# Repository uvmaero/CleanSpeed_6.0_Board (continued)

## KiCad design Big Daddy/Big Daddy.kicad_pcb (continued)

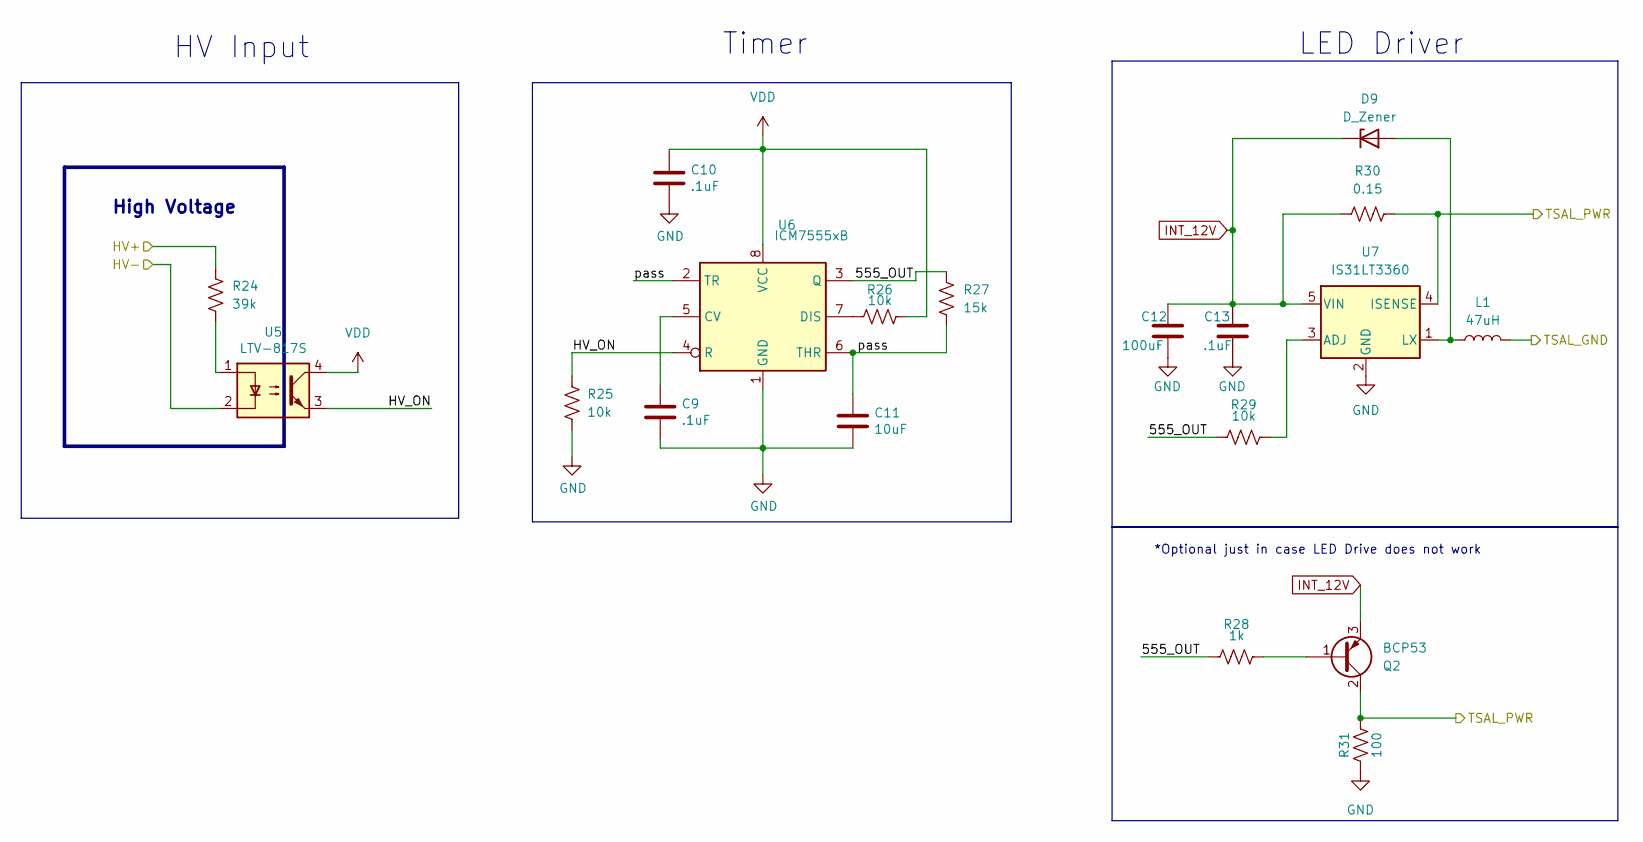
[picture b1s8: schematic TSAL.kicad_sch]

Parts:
C9, C10, C13: .1uF; C_0603_1608Metric_Pad1.08x0.95mm_HandSolder; Manufacturer_Part_Number CC0603KRX7R7BB104; Digikey part number 311-1088-1-ND
C11: 10uF; C_0603_1608Metric_Pad1.08x0.95mm_HandSolder; Manufacturer_Part_Number CL10A106KQ8NNNC; Digikey part number 1276-1038-1-ND
C12: 100uF; C_0603_1608Metric_Pad1.08x0.95mm_HandSolder
D9: D_Zener; D_SOD-123; Manufacturer_Part_Number MMSZ5231B-7-F; Digikey part number MMSZ5231B-FDICT-ND
L1: 47uH; L_0603_1608Metric_Pad1.05x0.95mm_HandSolder; Manufacturer_Part_Number LBMF1608T470K; Digikey part number 587-1716-1-ND
Q2: BCP53; SOT-223-3_TabPin2; Manufacturer_Part_Number BCP53; Digikey part number BCP53FSCT-ND
R24: 39k; R_Axial_DIN0414_L11.9mm_D4.5mm_P15.24mm_Horizontal; Manufacturer_Part_Number CF12JT39K0; Digikey part number CF12JT39K0CT-ND
R25, R26, R29: 10k; R_0603_1608Metric_Pad0.98x0.95mm_HandSolder; Manufacturer_Part_Number RK73H1JTTD1002F; Digikey part number 2019-RK73H1JTTD1002FCT-ND
R27: 15k; R_0603_1608Metric_Pad0.98x0.95mm_HandSolder; Manufacturer_Part_Number ERA-3AEB153V; Digikey part number P15KDBCT-ND
R28: 1k; R_0603_1608Metric_Pad0.98x0.95mm_HandSolder; Manufacturer_Part_Number RMCF0603FT1K00; Digikey part number RMCF0603FT1K00CT-ND
R30: 0.15; R_0603_1608Metric_Pad0.98x0.95mm_HandSolder; Manufacturer_Part_Number RL0603FR-070R15L; Digikey part number 311-.15QCT-ND
R31: 100; R_1206_3216Metric_Pad1.30x1.75mm_HandSolder; Manufacturer_Part_Number ERJ-8ENF1000V; Digikey part number P100FCT-ND
U5: LTV-817S; SMDIP-4_W9.53mm; Manufacturer_Part_Number LTV-817S; Digikey part number 160-1367-5-ND
U6: ICM7555xB; SOIC-8_3.9x4.9mm_P1.27mm; Manufacturer_Part_Number ICM7555CBAZ-T; Digikey part number ICM7555CBAZ-TCT-ND
U7: IS31LT3360; SOT-89-5; Manufacturer_Part_Number IS31LT3360-SDLS4-TR; Digikey part number 2521-IS31LT3360-SDLS4-TRCT-ND

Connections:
/Connectors/TSAL_GND: L1.2; also elsewhere on the board
/Connectors/TSAL_PWR: Q2.2 (C), Q2.4 (C), R30.2, R31.2, U7.4 (ISENSE); also elsewhere on the board
/High Voltage/TSAL/555_OUT: R27.1, R28.1, R29.1, U6.3 (Q)
/High Voltage/TSAL/HV+: R24.1; also elsewhere on the board
/High Voltage/TSAL/HV-: U5.2; also elsewhere on the board
/High Voltage/TSAL/HV_ON: R25.1, U5.3, U6.4 (R)
/High Voltage/TSAL/pass: C11.1, R27.2, U6.2 (TR), U6.6 (THR)
GND: C9.2, C10.2, C11.2, C12.1, C13.1, R25.2, R31.1, U6.1 (GND), U7.2 (GND); also elsewhere on the board
INT_12V: C12.2, C13.2, D9.1 (K), Q2.3 (E), R30.1, U7.5 (VIN); also elsewhere on the board
unnamed: D9.2 (A), L1.1, U7.1 (LX)
unnamed: Q2.1 (B), R28.2
unnamed: R24.2, U5.1
unnamed: C9.1, U6.5 (CV)
unnamed: R26.1, U6.7 (DIS)
unnamed: R29.2, U7.3 (ADJ)
VDD: C10.1, R26.2, U5.4, U6.8 (VCC); also elsewhere on the board

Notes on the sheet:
*Optional just in case LED Drive does not work
LED Driver
High Voltage
HV Input
Timer

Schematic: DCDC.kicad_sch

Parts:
C14, C15: 0.68uF; C_Rect_L18.0mm_W8.0mm_P15.00mm_FKS3_FKP3
C16, C17: 4700uF; C_Radial_D18.0mm_H35.5mm_P7.50mm
L2: 1uH; L_1008_2520Metric_Pad1.43x2.20mm_HandSolder; Manufacturer_Part_Number LQM2HPN1R0MG0L; Digikey part number 490-5112-1-ND
L3: 0.15uH; L_0805_2012Metric_Pad1.15x1.40mm_HandSolder; Manufacturer_Part_Number CE201210-R15J; Digikey part number CE201210-R15JCT-ND
R35, R40: 1; R_2512_6332Metric_Pad1.40x3.35mm_HandSolder; Manufacturer_Part_Number RK73H1JTTD1002F; Digikey part number 2019-RK73H1JTTD1002FCT-ND
R36: 300; R_0603_1608Metric_Pad0.98x0.95mm_HandSolder; Manufacturer_Part_Number ERJ-3GEYJ301V; Digikey part number P300GCT-ND
R37, R38, R39: 1k; R_0603_1608Metric_Pad0.98x0.95mm_HandSolder; Manufacturer_Part_Number RMCF0603FT1K00; Digikey part number RMCF0603FT1K00CT-ND
RV1: 50k TC33x-2-503E; Potentiometer_Bourns_TC33X_Vertical; Manufacturer_Part_Number TC33X-2-503E; Digikey part number TC33X-503ECT-ND
U8: Vicor_AERO; vicor-socket-no-cutouts
U9: LTV-817S; SMDIP-4_W9.53mm; Manufacturer_Part_Number LTV-817S; Digikey part number 160-1367-5-ND
U10: TLP184; MFSOP6-4_4.4x3.6mm_P1.27mm; Manufacturer_Part_Number TLP184(BL-TPL,SE; Digikey part number TLP184(BL-TPLSECT-ND

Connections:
/Fusing/Vicor_In: C17.1, L3.2, R40.1; also elsewhere on the board
/High Voltage/DCDC/EN_HV: U8.3 (EN), U9.4
/High Voltage/DCDC/FAULT_HV: R37.2, U8.4 (FT)
/High Voltage/DCDC/HV+: L2.1, R35.2; also elsewhere on the board
/High Voltage/DCDC/HV-: C14.2, C15.2, RV1.1, U8.5 (-IN), U9.3, U10.3; also elsewhere on the board
/High Voltage/DCDC/TRIM_HV: R36.1, U8.2 (TR)
/High Voltage/Vicor_Enable: R38.1, R39.2; also elsewhere on the board
/High Voltage/Vicor_Fault: U10.6; also elsewhere on the board
GND: C16.2, C17.2, U8.8 (-OUT), U9.2, U10.4; also elsewhere on the board
unnamed: R36.2, RV1.2
unnamed: R37.1, U10.1
unnamed: R38.2, U9.1
unnamed: C14.1, C15.1, L2.2, R35.1, U8.1 (+IN)
unnamed: C16.1, L3.1, R40.2, U8.9 (+OUT)
VDD: R39.1; also elsewhere on the board

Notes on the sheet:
HV Side is pulled high enternally, optoisolator turns on (with high signal) to pull en_hv low
Willem Hillier UVM AERO 3/5/2019
Trim Control
Input Filtering
HV->12V DC-DC
DC/DC out
Output Filtering
HV Danger!
Pull high to disable
500V-rated caps
HV-Interface
FAULT_HV can only supply 4mA absolute max, hence the different optocoupler choice.

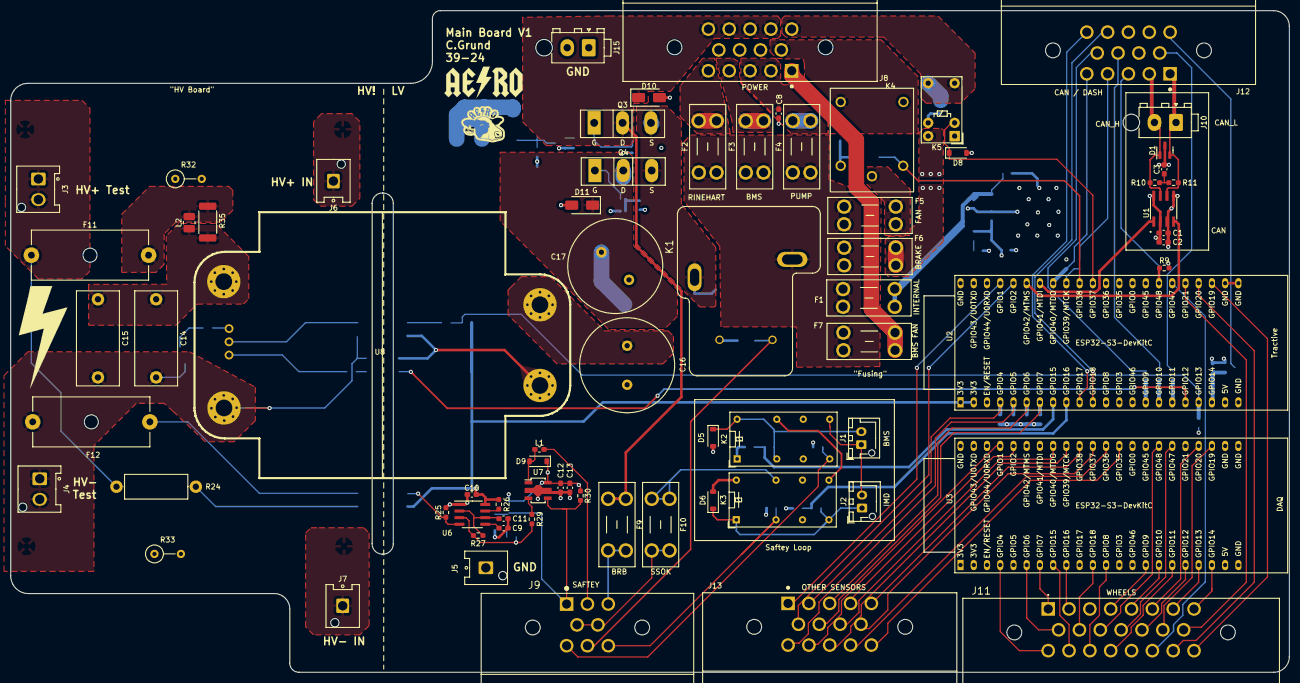
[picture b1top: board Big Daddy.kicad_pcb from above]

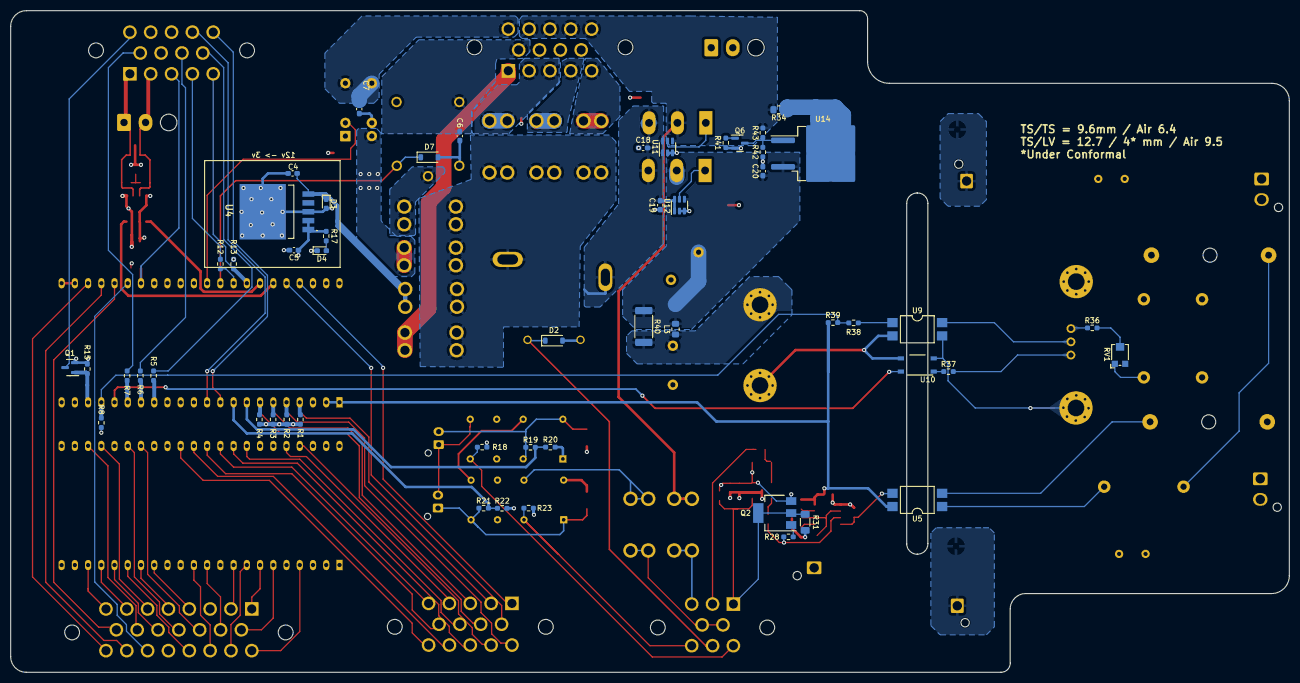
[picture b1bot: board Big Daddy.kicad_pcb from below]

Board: 4 copper layers, 245.4 x 126.9 mm, 124 parts (52 on the bottom side), 115 nets.

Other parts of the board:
Q6: MMBT2222; SOT-23
R41: 100; R_0603_1608Metric_Pad0.98x0.95mm_HandSolder

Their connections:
GND: Q6.2 (E), R41.2; also elsewhere on the board
unnamed: Q6.1 (B), R41.1

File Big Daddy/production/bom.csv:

Designator,Footprint,Quantity,Value,LCSC Part #
"C1, C10, C13, C18, C19, C2, C20, C3, C9",0603,9,.1uF,
"C11, C4, C6, C7, C8",0603,5,10uF,
C12,0603,1,100uF,
"C14, C15",C_Rect_L18.0mm_W8.0mm_P15.00mm_FKS3_FKP3,2,0.68uF,
"C16, C17",C_Radial_D18.0mm_H35.5mm_P7.50mm,2,4700uF,
C5,0603,1,22uF,
D1,SOT-23,1,DESD2CAN2SOQ-7,
"D10, D11",D_SMA,2,SS16,
"D2, D5, D6, D7, D8",D_SOD-123,5,1N4148W,
D3,0603,1,TS4148C RZG,
D4,0603,1,LED,
D9,D_SOD-123,1,D_Zener,
"F1, F4, F6, F7",Fuseholder_Blade_Mini_Keystone_3568,4,2A,
"F10, F9",Fuseholder_Blade_Mini_Keystone_3568,2,1A,
F11,Fuseholder_Cylinder-5x20mm_Schurter_0031_8201_Horizontal_Open_3d,1,5A,
F12,Fuseholder_Cylinder-5x20mm_Schurter_0031_8201_Horizontal_Open_3d,1,1A,
F2,Fuseholder_Blade_Mini_Keystone_3568,1,10A,
"F3, F5",Fuseholder_Blade_Mini_Keystone_3568,2,5A,
J1,JST_XH_B2B-XH-AM_1x02_P2.50mm_Vertical,1,BMS Button,
"J10, J15",TE_MATE-N-LOK_1-770866-x_1x02_P4.14mm_Vertical,2,Conn_01x02,
J11,TE_1-770669-1_23pin_Horizontal,1,Conn_01x23,
"J12, J13, J8",TE_1-776266-1_14pin_Horizontal,3,Conn_01x14,
J2,JST_XH_B2B-XH-AM_1x02_P2.50mm_Vertical,1,IMD Button,
J3,Hirose_DF63R-2P-3.96DSA_1x02_P3.96mm_Vertical,1,HV+,
J4,Hirose_DF63R-2P-3.96DSA_1x02_P3.96mm_Vertical,1,HV-,
J5,Hirose_DF63M-1P-3.96DSA_1x01_P3.96mm_Vertical,1,GND,
J6,Hirose_DF63M-1P-3.96DSA_1x01_P3.96mm_Vertical,1,HV+,
J7,Hirose_DF63M-1P-3.96DSA_1x01_P3.96mm_Vertical,1,HV-,
J9,TE_1-776280-1_8pin_Horizontal,1,Conn_01x08,
K1,RELAY_T9VV1K15-12S,1,T9VV1K15-12S,
"K2, K3",Relay_DPDT_Omron_G5V-2,2,G5V-2,
K4,J1071AS3VDC,1,J107,
K5,Relay_SPDT_Omron_G5V-1,1,G5V-1,
L1,0603,1,47uH,
L2,1008,1,1uH,
L3,0805,1,0.15uH,
Q1,SOT-23,1,2N7002,
Q2,SOT-223-3_TabPin2,1,BCP53,
"Q3, Q4",TO-247-3_Vertical_GDS,2,IXFH34N65X2,
Q6,SOT-23,1,MMBT2222,
"R1, R13, R15, R18, R2, R23, R25, R26, R29, R3, R4, R8, R9",0603,13,10k,
"R10, R11",0603,2,60,
"R12, R17, R5, R6, R7",0603,5,330,
"R19, R21",0603,2,5.97k,
"R20, R22",0603,2,2.2k,
R24,R_Axial_DIN0414_L11.9mm_D4.5mm_P15.24mm_Horizontal,1,39k,
R27,0603,1,15k,
"R28, R37, R38, R39",0603,4,1k,
R30,0603,1,0.15,
R31,1206,1,100,
"R32, R33",R_Axial_DIN0309_L9.0mm_D3.2mm_P5.08mm_Vertical,2,20k,
R34,0805,1,.2,
"R35, R40",2512,2,1,
R36,0603,1,300,
R41,0603,1,100,
R42,0603,1,2.4k,
R43,0603,1,240,
RV1,Potentiometer_Bourns_TC33X_Vertical,1,50k TC33x-2-503E,
U1,SOIC127P600X175-8N,1,MAX33054EASA+T,
U10,MFSOP6-4_4.4x3.6mm_P1.27mm,1,TLP184,
"U11, U12",TSOT-23-6,2,LM5050-1,
U14,TO-263-2,1,LM317_TO-263,
"U2, U3",ESP32-S3-DevKitC,2,ESP32-S3-DevKitC,
U4,LT1528CQPBF,1,LT1528CQ#PBF,
"U5, U9",SMDIP-4_W9.53mm,2,LTV-817S,
U6,SOIC-8_3.9x4.9mm_P1.27mm,1,ICM7555xB,
U7,SOT-89-5,1,IS31LT3360,
U8,vicor-socket-no-cutouts,1,Vicor_AERO,

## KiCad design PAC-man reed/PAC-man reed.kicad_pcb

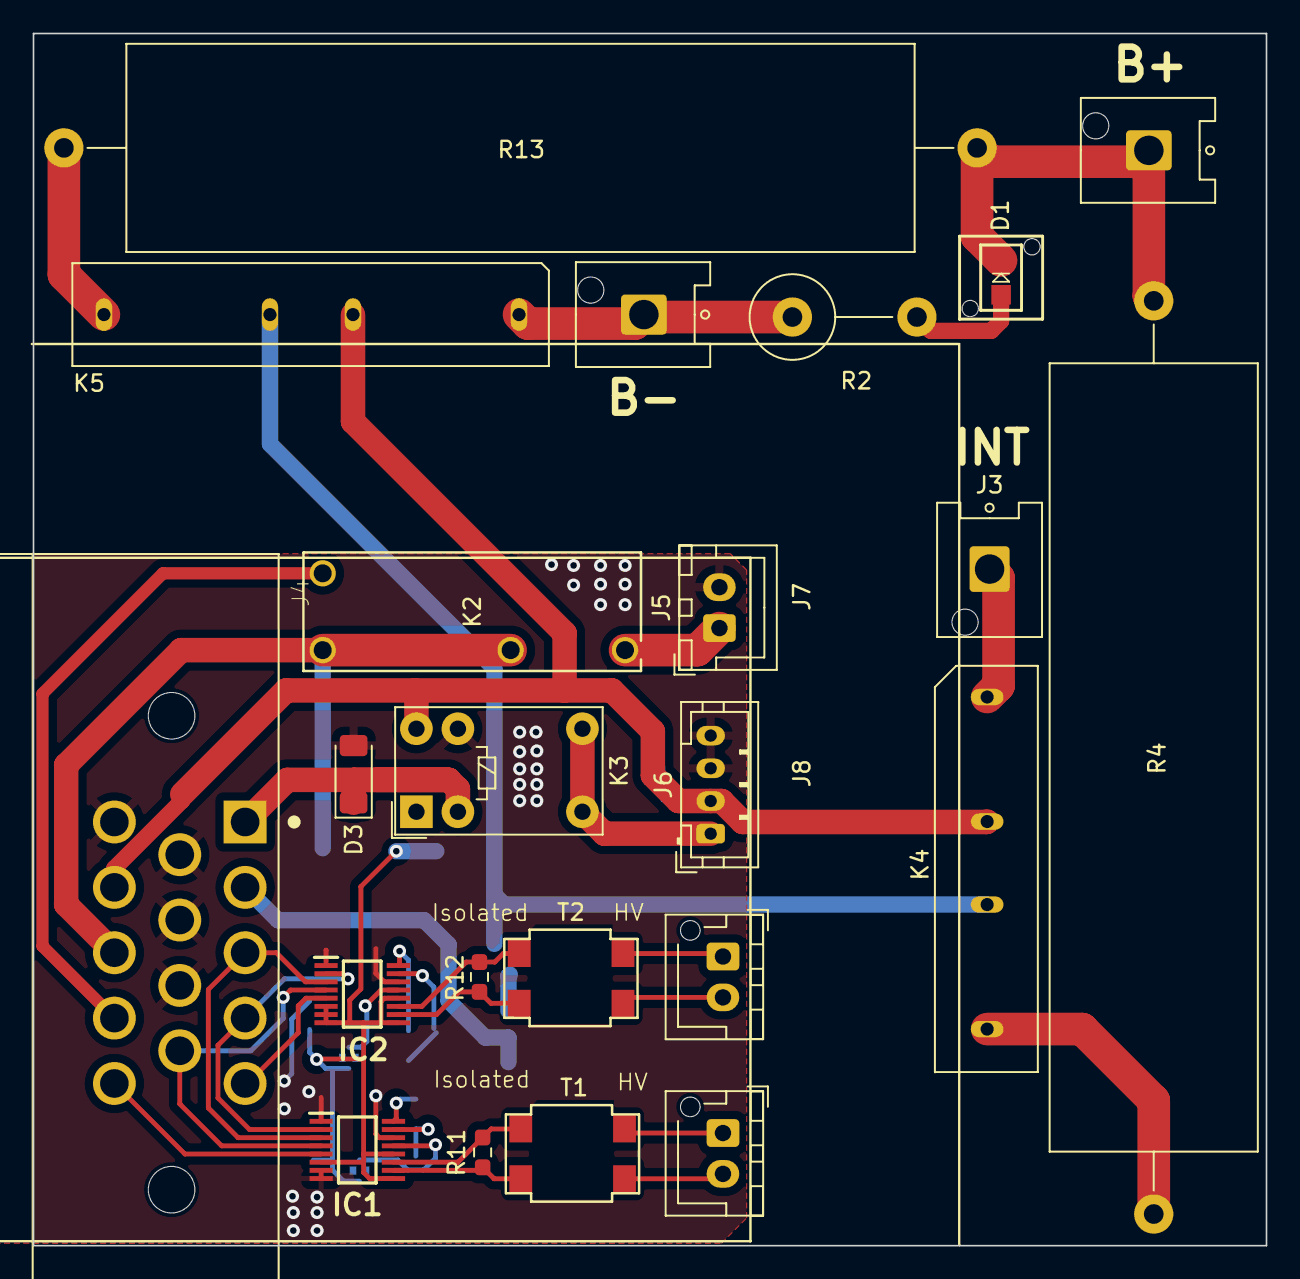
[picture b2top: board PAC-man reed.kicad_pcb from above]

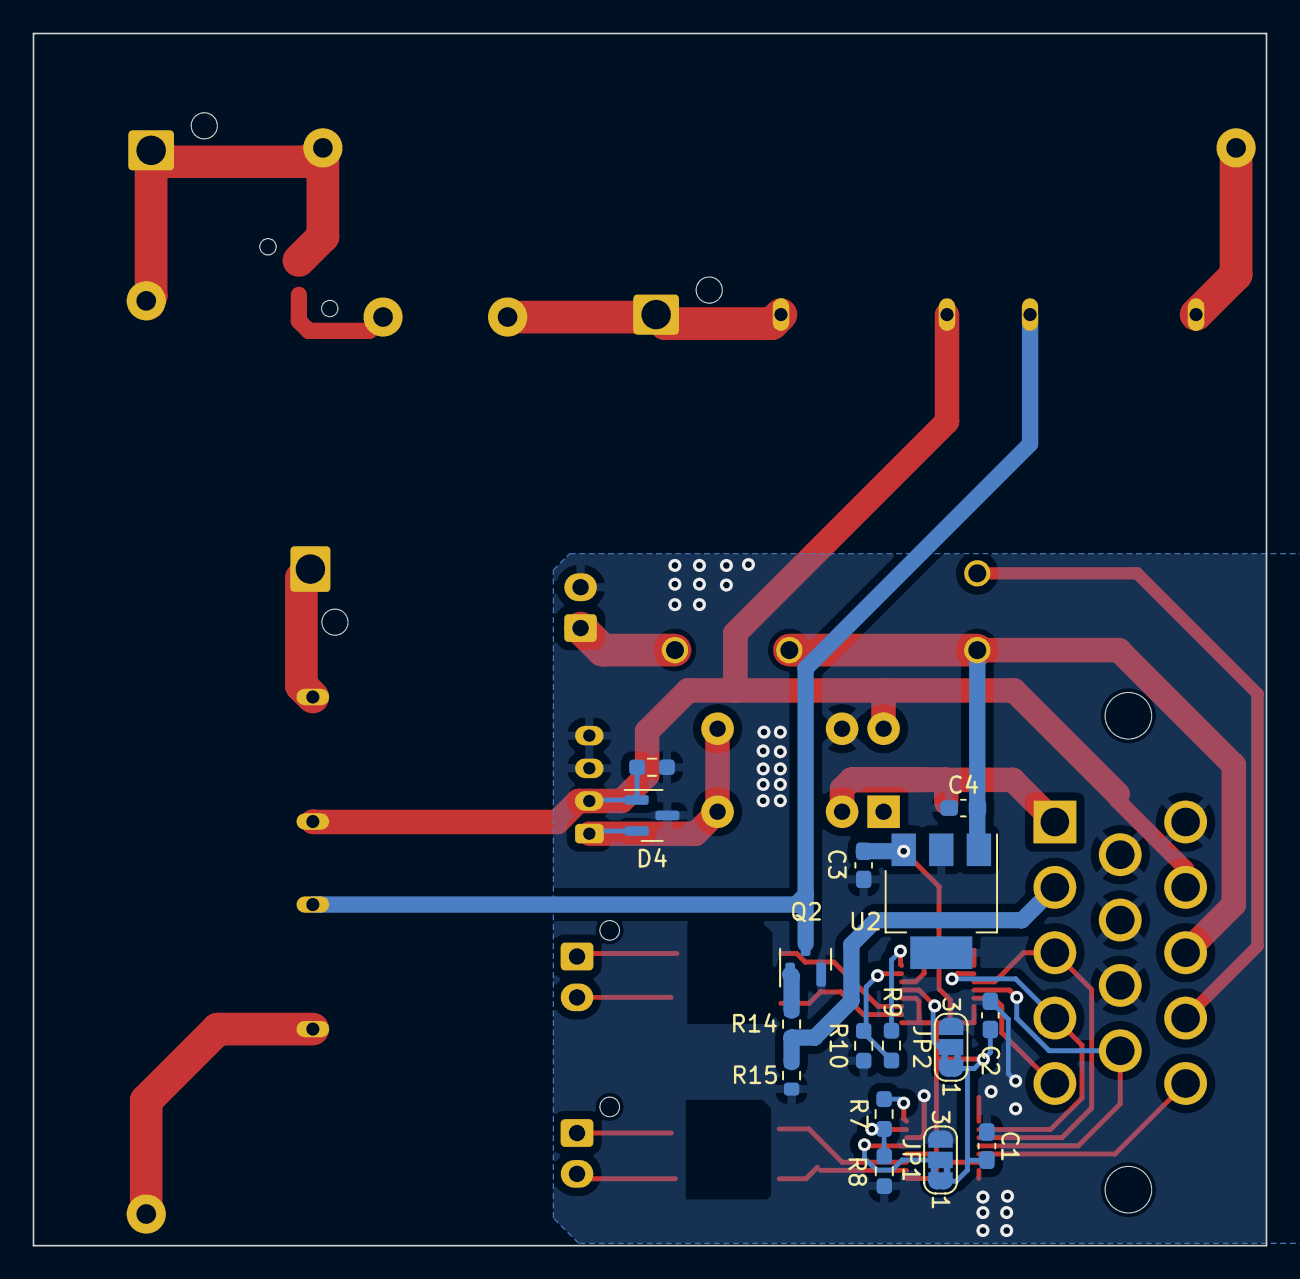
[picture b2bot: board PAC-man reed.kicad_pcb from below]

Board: 2 copper layers, 75.5 x 74.2 mm, 39 parts (16 on the bottom side), 36 nets.

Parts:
C1, C2: 0.01u; C_0603_1608Metric_Pad1.08x0.95mm_HandSolder
C3, C4: 10u; C_0603_1608Metric_Pad1.08x0.95mm_HandSolder
D1: LED; LPA-C011301S-x LED 0805 LIGHT PIPE SINGLE VERT SMD
D3: 1N4148; D_MiniMELF
D4: MMBZxx; SOT-23
IC1, IC2: LTC6820HMS#3ZZPBF; SOP50P490X110-16N
J1, J2, J3: Conn_01x01; Hirose_DF63M-1P-3.96DSA_1x01_P3.96mm_Vertical
J4: Conn_01x14; TE_1-776266-1_14pin_Horizontal
J5: Conn_01x02; JST_XH_B2B-XH-A_1x02_P2.50mm_Vertical
J6: JST PH; JST_PH_B4B-PH-K_1x04_P2.00mm_Vertical
J7, J8: Conn_01x02; JST_XH_B2B-XH-AM_1x02_P2.50mm_Vertical
JP1, JP2: Fast / Slow; SolderJumper-3_P1.3mm_Bridged2Bar12_RoundedPad1.0x1.5mm_Num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
K2: G5NB-1A4-E DC12; RELAY_G5NB-1A DC5_OMR
K3: G5V-1; Relay_SPDT_Omron_G5V-1
K4: 374-1408-5-ND; SHV12
K5: S1-12-BDM; S1-12
Q2: MMBT2222A; SOT-23
R2: 1.5k; R_Axial_DIN0516_L15.5mm_D5.0mm_P7.62mm_Vertical
R4: 2.5K; R_Axial_Power_L48.0mm_W12.5mm_P55.88mm
R5: 15k; R_0603_1608Metric_Pad0.98x0.95mm_HandSolder
R7, R8, R9, R10: 1k; R_0603_1608Metric_Pad0.98x0.95mm_HandSolder
R11, R12: 60; R_0603_1608Metric_Pad0.98x0.95mm_HandSolder
R13: 2.5k; R_Axial_Power_L48.0mm_W12.5mm_P55.88mm
R14: 10k; R_0603_1608Metric
R15: 2k; R_0603_1608Metric
T1, T2: ESMIT-4180_C; SOIC4_CBM4D19_SUM
U2: LT1963AxST-3.3; SOT-223-3_TabPin2

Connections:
+3.3V: C1.1, C2.1, C3.1, IC1.6 (VDDS), IC1.9 (VDD), IC1.12 (MSTR), IC2.6 (VDDS), IC2.7 (POL), IC2.8 (PHA), IC2.9 (VDD), IC2.12 (MSTR), JP1.1 (A), JP2.1 (A), U2.3 (OUT)
+12V: C4.1, J4.12, K2.1, K2.2, U2.1 (IN)
/AIR_B+: D4.2 (K), J6.1, K3.5, K3.6
/AIR_B-: D4.1 (K), J4.11, J6.2, K3.10, K4.2, K5.2, R5.2
/B+: J2.1, K5.1, R2.1
/B-: D1.1 (K), J1.1, R4.1, R13.1
/CS1: IC1.5 (~CS), J4.14
/CS2: IC2.5 (~CS), J4.5
/FAN: J4.13, K2.4
/FAN_OUT: J5.1, K2.3
/INT: J3.1, K4.1
/IsoSpi/IMA1: J7.2, T1.3
/IsoSpi/IMA2: J8.2, T2.3
/IsoSpi/IPA1: J7.1, T1.4
/IsoSpi/IPA2: J8.1, T2.4
/MAIN_CONT: D3.1 (K), J4.1, K3.2
/MISO: IC1.3 (MISO), IC2.3 (MISO), J4.3
/MOSI: IC1.2 (MOSI), IC2.2 (MOSI), J4.4
/PRECHARGE: J4.2, R14.2, R15.2
/Relay_Drive: K4.3, K5.3, Q2.3 (C)
/SCK: IC1.4 (SCK), IC2.4 (SCK), J4.9
GND: C1.2, C2.2, C3.2, C4.2, D3.2 (A), D4.3 (A), IC1.1 (EN), IC1.7 (POL), IC1.8 (PHA), IC1.14 (GND), IC2.1 (EN), IC2.14 (GND), J4.6, J4.7, J4.8, J4.10, J5.2, J6.3, J6.4, JP1.3 (B), JP2.3 (B), K3.9, Q2.2 (E), R5.1, R8.2, R10.2, R15.1, U2.2 (GND)
unnamed: D1.2 (A), R2.2
unnamed: IC1.16 (IBIAS), R7.1
unnamed: IC1.15 (ICMP), R7.2, R8.1
unnamed: IC1.10 (IM), R11.2, T1.2
unnamed: IC1.11 (IP), R11.1, T1.1
unnamed: IC1.13 (SLOW), JP1.2 (C)
unnamed: IC2.16 (IBIAS), R9.1
unnamed: IC2.15 (ICMP), R9.2, R10.1
unnamed: IC2.10 (IM), R12.2, T2.2
unnamed: IC2.11 (IP), R12.1, T2.1
unnamed: IC2.13 (SLOW), JP2.2 (C)
unnamed: K4.4, R4.2
unnamed: K5.4, R13.2
unnamed: Q2.1 (B), R14.1

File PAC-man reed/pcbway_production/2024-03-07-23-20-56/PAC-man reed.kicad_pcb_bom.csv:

designator,quantity,value,pack,mpn,mount_type
"C1, C2",2,0.01u,C_0603_1608Metric_Pad1.08x0.95mm_HandSolder,,smt
"C3, C4",2,10u,C_0603_1608Metric_Pad1.08x0.95mm_HandSolder,,smt
D1,1,LED,LPA-C011301S-x LED 0805 LIGHT PIPE SINGLE VERT SMD,,tht
D3,1,1N4148,D_MiniMELF,,smt
D4,1,MMBZxx,SOT-23,,smt
"IC1, IC2",2,LTC6820HMS#3ZZPBF,SOP50P490X110-16N,,smt
"J1, J2, J3",3,Conn_01x01,Hirose_DF63M-1P-3.96DSA_1x01_P3.96mm_Vertical,,tht
J4,1,Conn_01x14,TE_1-776266-1_14pin_Horizontal,,tht
J5,1,Conn_01x02,JST_XH_B2B-XH-A_1x02_P2.50mm_Vertical,,tht
J6,1,JST PH,JST_PH_B4B-PH-K_1x04_P2.00mm_Vertical,,tht
"J7, J8",2,Conn_01x02,JST_XH_B2B-XH-AM_1x02_P2.50mm_Vertical,,tht
"JP1, JP2",2,Fast / Slow,SolderJumper-3_P1.3mm_Bridged2Bar12_RoundedPad1.0x1.5mm_NumberLabels,,tht
K2,1,G5NB-1A4-E DC12,RELAY_G5NB-1A DC5_OMR,,tht
K3,1,G5V-1,Relay_SPDT_Omron_G5V-1,,tht
K4,1,374-1408-5-ND,SHV12,,tht
K5,1,S1-12-BDM,S1-12,,tht
Q2,1,MMBT2222A,SOT-23,,smt
"R10, R7, R8, R9",4,1k,R_0603_1608Metric_Pad0.98x0.95mm_HandSolder,,smt
"R11, R12",2,60,R_0603_1608Metric_Pad0.98x0.95mm_HandSolder,,smt
R13,1,2.5k,R_Axial_Power_L48.0mm_W12.5mm_P55.88mm,,tht
R14,1,10k,R_0603_1608Metric,,smt
R15,1,2k,R_0603_1608Metric,,smt
R2,1,1.5k,R_Axial_DIN0516_L15.5mm_D5.0mm_P7.62mm_Vertical,,tht
R4,1,2.5K,R_Axial_Power_L48.0mm_W12.5mm_P55.88mm,,tht
R5,1,15k,R_0603_1608Metric_Pad0.98x0.95mm_HandSolder,,smt
"T1, T2",2,ESMIT-4180_C,SOIC4_CBM4D19_SUM,,smt
U2,1,LT1963AxST-3.3,SOT-223-3_TabPin2,,smt

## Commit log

2023-05-15 DADDY BOARD
2024-01-09 delete
2024-01-09 Just need last circuit and traced but 90% done
    Pushing big daddy almost everything is where it needs to be might do net classes to make traces easier but timing. The schematic is 90% done trying to make a better charging circuit from vicor so no 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
2024-01-09 edge cuts
2024-01-11 Schematic DONE
2024-02-07 so cloes
2024-02-07 REVIEW TIME
2024-02-16 stuff
2024-02-26 board thats here
2024-05-02 post comp
2024-05-02 BMS added
2024-06-19 George Redlines for Big Daddy board
2024-09-16 big dump
2024-09-16 Revert "Update all"
2025-01-13 idk stuff
2025-04-10 Updated BOM
2025-09-22 2025 push
